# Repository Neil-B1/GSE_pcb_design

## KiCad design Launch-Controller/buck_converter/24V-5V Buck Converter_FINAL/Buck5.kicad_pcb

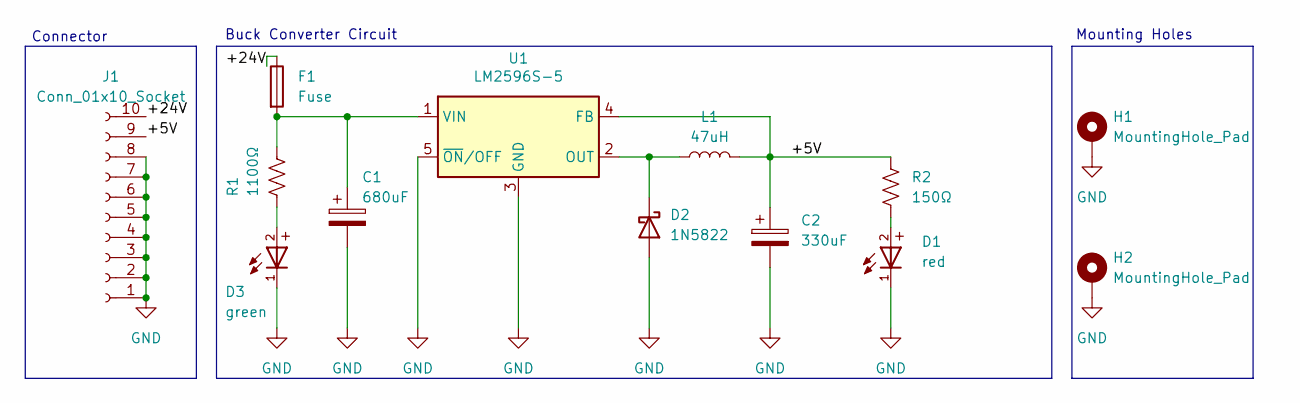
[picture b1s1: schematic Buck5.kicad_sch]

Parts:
C1: 680uF; CAPAE660X800N
C2: 330uF; CP_Radial_D8.0mm_P3.50mm
D1: red; LED_1206_3216Metric_Pad1.42x1.75mm_HandSolder
D2: 1N5822; D_DO-201AD_P15.24mm_Horizontal
D3: green; LED_0603_1608Metric_Pad1.05x0.95mm_HandSolder
F1: Fuse; D_0402_1005Metric_Pad0.77x0.64mm_HandSolder
H1, H2: MountingHole_Pad; MountingHole_3.7mm_Pad
J1: Conn_01x10_Socket; PRECI-DIP_310-87-110-41-001101
L1: 47uH; output inductor
R1: 1100Ω; R_1210_3225Metric_Pad1.30x2.65mm_HandSolder
R2: 150Ω; R_0805_2012Metric_Pad1.20x1.40mm_HandSolder
U1: LM2596S-5; TO-263-5_TabPin3

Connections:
/+5V: C2.1, J1.9, L1.2, R2.1, U1.4 (FB)
/+24V: F1.1, J1.10
GND: C1.2, C2.2, D1.1, D2.2 (A), D3.1, H1.1, H2.1, J1.1, J1.2, J1.3, J1.4, J1.5, J1.6, J1.7, J1.8, U1.3 (GND), U1.5 (~ON/OFF)
unnamed: D1.2, R2.2
unnamed: D2.1 (K), L1.1, U1.2 (OUT)
unnamed: D3.2, R1.2
unnamed: C1.1, F1.2, R1.1, U1.1 (VIN)

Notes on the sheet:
Connector
Buck Converter Circuit
Mounting Holes

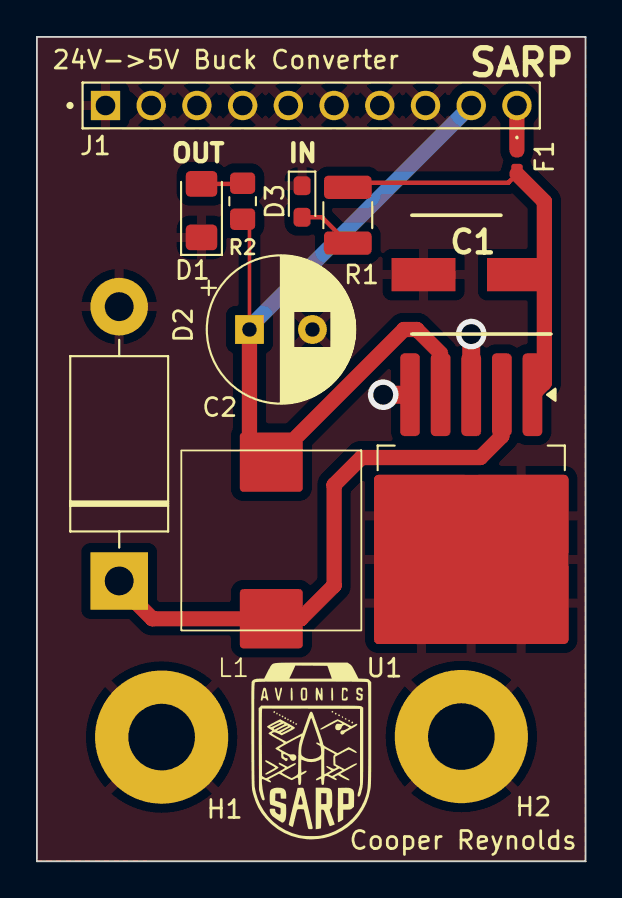
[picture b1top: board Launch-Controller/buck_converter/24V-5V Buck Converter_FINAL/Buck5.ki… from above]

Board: 4 copper layers, 30.5 x 45.8 mm, 13 parts (0 on the bottom side), 7 nets.

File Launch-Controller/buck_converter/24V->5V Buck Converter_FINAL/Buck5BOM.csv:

"Reference","Value","Datasheet","Footprint","Qty","DNP"
"C1","680uF","https://industrial.panasonic.com/cdbs/www-data/pdf/RDE0000/A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","Library:CAPAE660X800N","1",""
"C2","330uF","https://industrial.panasonic.com/cdbs/www-data/pdf/RDF0000/A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","Capacitor_THT:CP_Radial_D8.0mm_P3.50mm","1",""
"D1","red","https://www.mouser.com/datasheet/2/50/SM1206HC-3001920.pdf","LED_SMD:LED_1206_3216Metric_Pad1.42x1.75mm_HandSolder","1",""
"D2","1N5822","http://www.vishay.com/docs/88526/1n5820.pdf","Diode_THT:D_DO-201AD_P15.24mm_Horizontal","1",""
"D3","green","https://www.mouser.com/datasheet/2/50/SM0603PGC-3001706.pdf","LED_SMD:LED_0603_1608Metric_Pad1.05x0.95mm_HandSolder","1",""
"F1","Fuse","https://industrial.panasonic.com/cdbs/www-data/pdf/AFA0000/A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","Diode_SMD:D_0402_1005Metric_Pad0.77x0.64mm_HandSolder","1",""
"J1","Conn_01x10_Socket","https://precidip.com/product/310-87-110-41-001101/","Library:PRECI-DIP_310-87-110-41-001101","1",""
"L1","47uH","bourns.com/docs/Product-Datasheets/SRP1038A.pdf","Library:output inductor","1",""
"R1","1100Ω","https://www.vishay.com/docs/20043/crcwhpe3.pdf","Resistor_SMD:R_1210_3225Metric_Pad1.30x2.65mm_HandSolder","1",""
"R2","150Ω","https://fscdn.rohm.com/en/products/databook/datasheet/passiv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","Resistor_SMD:R_0805_2012Metric_Pad1.20x1.40mm_HandSolder","1",""
"U1","LM2596S-5","http://www.ti.com/lit/ds/symlink/lm2596.pdf","Package_TO_SOT_SMD:TO-263-5_TabPin3","1",""

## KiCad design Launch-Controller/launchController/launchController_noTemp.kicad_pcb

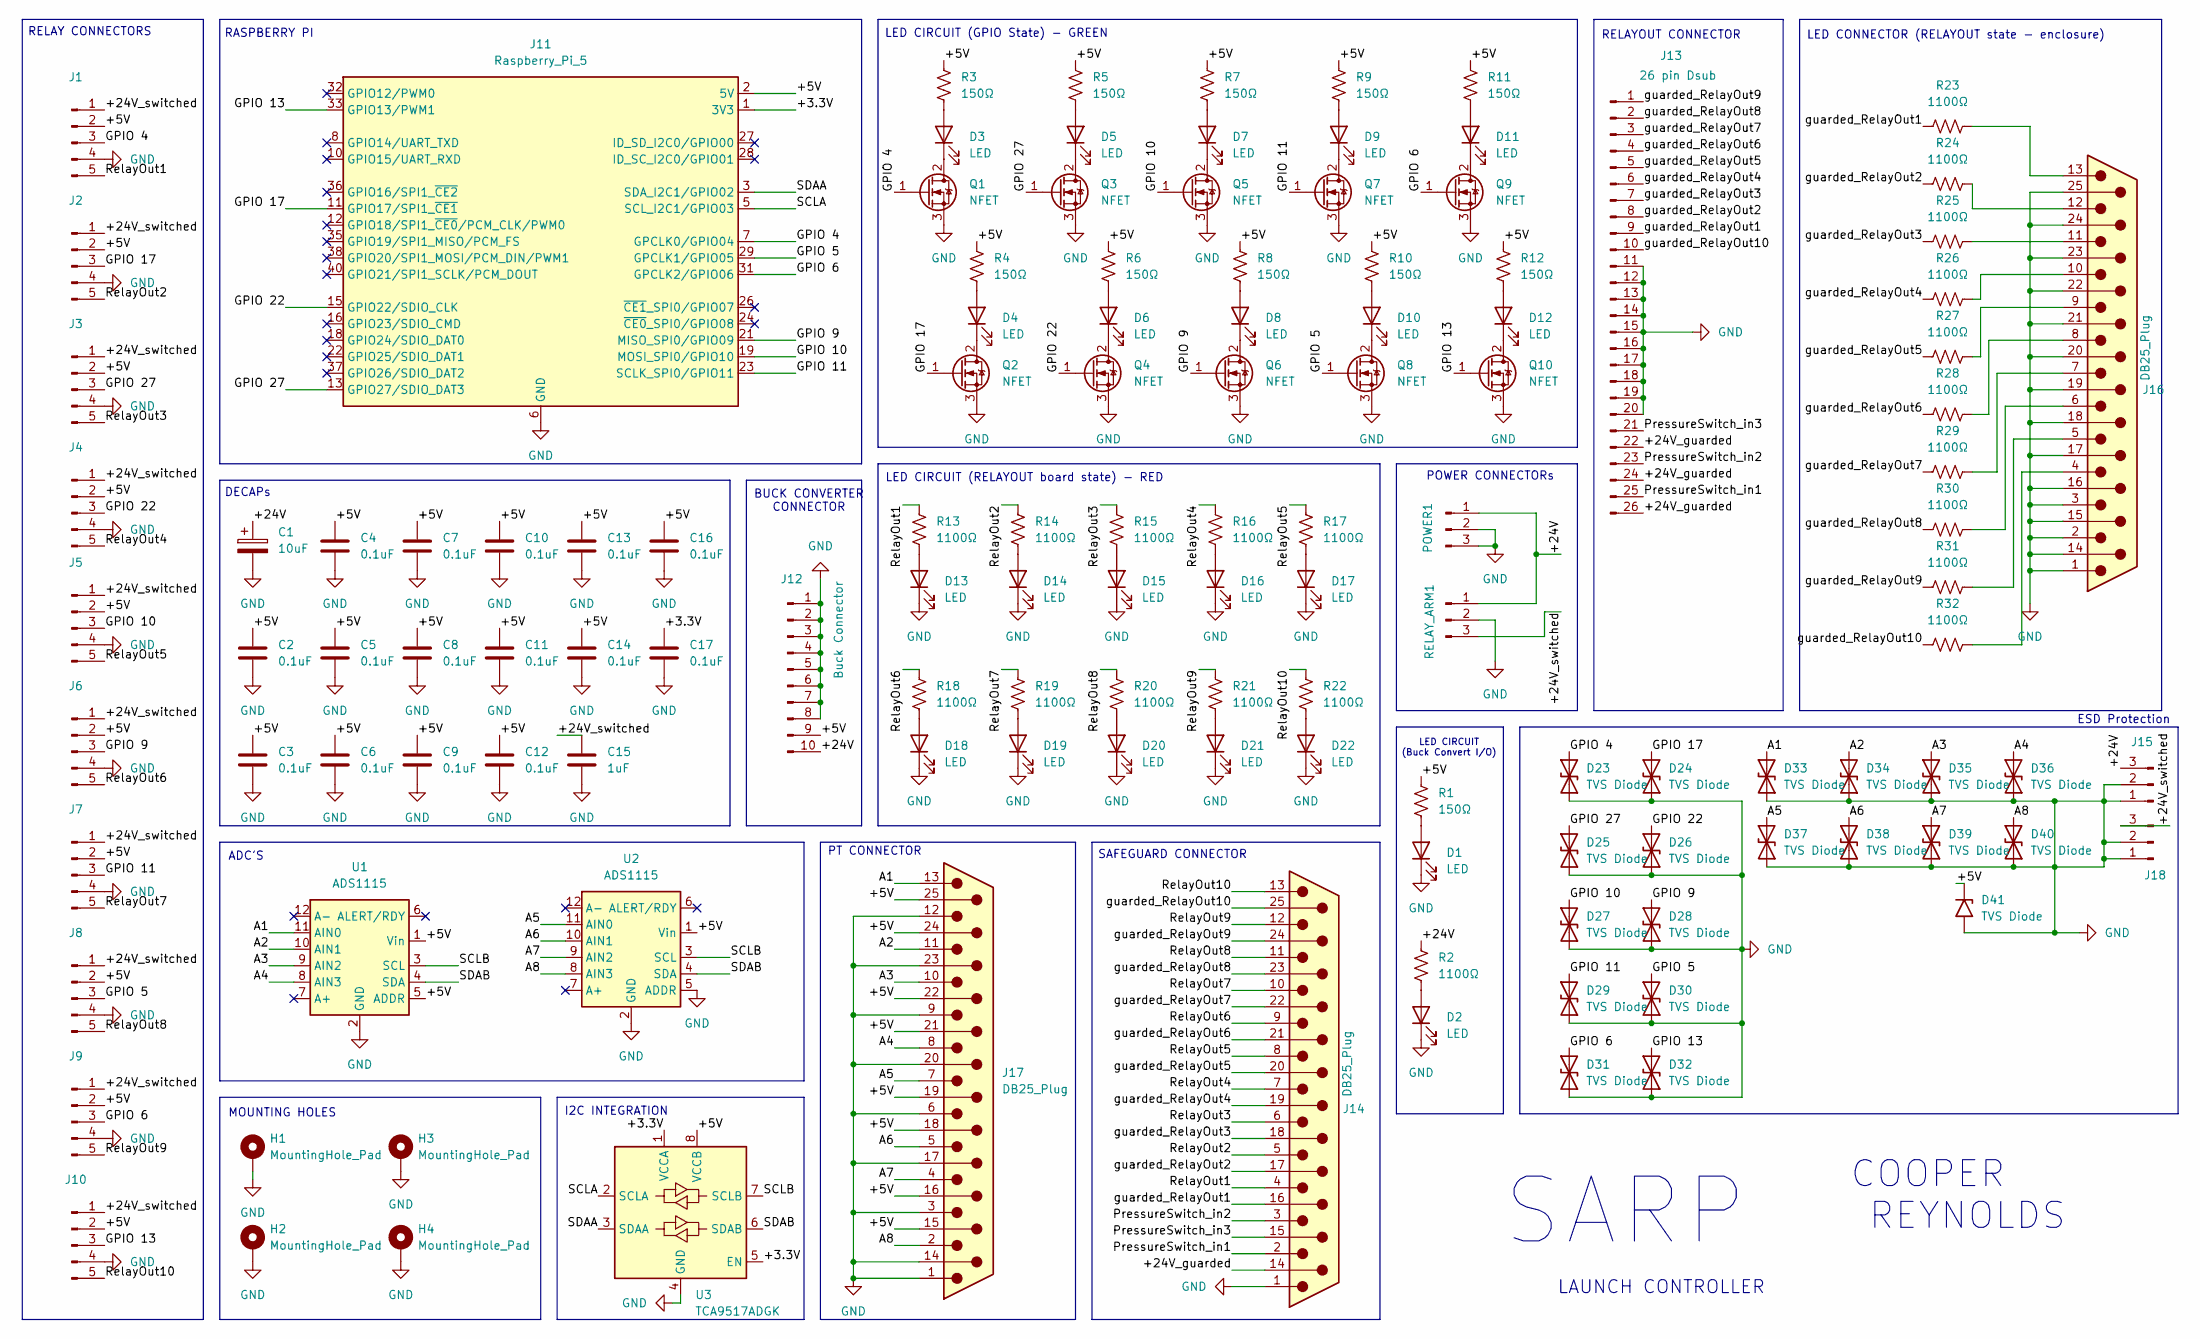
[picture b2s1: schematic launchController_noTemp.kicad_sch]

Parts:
C1: 10uF; CP_Radial_D6.3mm_P2.50mm
C2, C3, C4, C5, C6, C7, C8, C9, C10, C11, C12, C13, C14, C16, C17: 0.1uF; C_0402_1005Metric_Pad0.74x0.62mm_HandSolder
C15: 1uF; C_Axial_L5.1mm_D3.1mm_P7.50mm_Horizontal
D1, D13, D14, D15, D16, D17, D18, D19, D20, D21, D22: LED; LED_1206_3216Metric_Pad1.42x1.75mm_HandSolder
D2, D3, D4, D5, D6, D7, D8, D9, D10, D11, D12: LED; LED_0603_1608Metric_Pad1.05x0.95mm_HandSolder
D23, D24, D25, D26, D27, D28, D29, D30, D31, D32: TVS Diode; D_SOD-923
D33, D34, D35, D36, D37, D38, D39, D40: TVS Diode; D_SOD-523
D41: TVS Diode; D_SOD-323_HandSoldering
H1, H2, H3, H4: MountingHole_Pad; MountingHole_3.7mm_Pad
J1, J2, J3, J4, J5, J6, J7, J8, J9, J10: Relay Connector; RelaySwitch Connector
J11: Raspberry_Pi_5; RPi_5_upside_down
J12: Buck Connector; BuckConverter Connector
J13: 26 pin Dsub; DSUB-26-HD_Female_Horizontal_P2.29x1.98mm_EdgePinOffset8.35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
J14, J16, J17: DB25_Plug; DSUB-25_Female_Horizontal_P2.77x2.84mm_EdgePinOffset7.70mm_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
J15, J18: TVS Diode; SOT-23-3
POWER1: Power Connector; 684M3W3203L461
Q1, Q2, Q3, Q4, Q5, Q6, Q7, Q8, Q9, Q10: NFET; SOT-23-3
R1: 150Ω; R_0805_2012Metric_Pad1.20x1.40mm_HandSolder
R2, R13, R14, R15, R16, R17, R18, R19, R20, R21, R22, R23, R24, R25, R26, R27, R28, R29, R30, R31, R32: 1100Ω; R_1210_3225Metric_Pad1.30x2.65mm_HandSolder
R3, R4, R5, R6, R7, R8, R9, R10, R11, R12: 150Ω; R_0805_2012Metric_Pad1.20x1.40mm_HandSolder
RELAY_ARM1: Power Connector; 684M3W3203L461
U1, U2: ADS1115
U3: TCA9517ADGK; Texas_S-PDSO-G8_3x3mm_P0.65mm

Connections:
/+3.3V: C17.1, J11.1 (3V3), J11.17 (3V3), U3.1 (VCCA), U3.5 (EN)
/+5V: C2.1, C3.1, C4.1, C5.1, C6.1, C7.1, C8.1, C9.1, C10.1, C11.1, C12.1, C13.1, C14.1, C16.1, D41.1 (A1), J1.2, J2.2, J3.2, J4.2, J5.2, J6.2, J7.2, J8.2, J9.2, J10.2, J11.2 (5V), J11.4 (5V), J12.9, J17.15, J17.16, J17.18, J17.19, J17.21, J17.22, J17.24, J17.25, R1.1, R3.1, R4.1, R5.1, R6.1, R7.1, R8.1, R9.1, R10.1, R11.1, R12.1, U1.1 (Vin), U1.5 (ADDR), U2.1 (Vin), U3.8 (VCCB)
/+24V: C1.1, J12.10, J15.3, POWER1.1, R2.1, RELAY_ARM1.1
/+24V_guarded: J13.22, J13.24, J13.26, J14.14
/+24V_switched: C15.1, J1.1, J2.1, J3.1, J4.1, J5.1, J6.1, J7.1, J8.1, J9.1, J10.1, J18.3, RELAY_ARM1.3
/A1: D33.2 (A2), J17.13, U1.11 (AIN0)
/A2: D34.2 (A2), J17.11, U1.10 (AIN1)
/A3: D35.2 (A2), J17.10, U1.9 (AIN2)
/A4: D36.2 (A2), J17.8, U1.8 (AIN3)
/A5: D37.2 (A2), J17.7, U2.11 (AIN0)
/A6: D38.2 (A2), J17.5, U2.10 (AIN1)
/A7: D39.2 (A2), J17.4, U2.9 (AIN2)
/A8: D40.2 (A2), J17.2, U2.8 (AIN3)
/GPIO 4: D23.2 (A2), J1.3, J11.7 (GPCLK0/GPIO04), Q1.1 (G)
/GPIO 5: D30.2 (A2), J8.3, J11.29 (GPCLK1/GPIO05), Q8.1 (G)
/GPIO 6: D31.2 (A2), J9.3, J11.31 (GPCLK2/GPIO06), Q9.1 (G)
/GPIO 9: D28.2 (A2), J6.3, J11.21 (MISO_SPI0/GPIO09), Q6.1 (G)
/GPIO 10: D27.2 (A2), J5.3, J11.19 (MOSI_SPI0/GPIO10), Q5.1 (G)
/GPIO 11: D29.2 (A2), J7.3, J11.23 (SCLK_SPI0/GPIO11), Q7.1 (G)
/GPIO 13: D32.2 (A2), J10.3, J11.33 (GPIO13/PWM1), Q10.1 (G)
/GPIO 17: D24.2 (A2), J2.3, J11.11 (GPIO17/SPI1_~CE1), Q2.1 (G)
/GPIO 22: D26.2 (A2), J4.3, J11.15 (GPIO22/SDIO_CLK), Q4.1 (G)
/GPIO 27: D25.2 (A2), J3.3, J11.13 (GPIO27/SDIO_DAT3), Q3.1 (G)
/PressureSwitch_in1: J13.25, J14.2
/PressureSwitch_in2: J13.23, J14.3
/PressureSwitch_in3: J13.21, J14.15
/RelayOut1: J1.5, J14.4, R13.1
/RelayOut2: J2.5, J14.5, R14.1
/RelayOut3: J3.5, J14.6, R15.1
/RelayOut4: J4.5, J14.7, R16.1
/RelayOut5: J5.5, J14.8, R17.1
/RelayOut6: J6.5, J14.9, R18.1
/RelayOut7: J7.5, J14.10, R19.1
/RelayOut8: J8.5, J14.11, R20.1
/RelayOut9: J9.5, J14.12, R21.1
/RelayOut10: J10.5, J14.13, R22.1
/SCLA: J11.5 (SCL_I2C1/GPIO03), U3.2 (SCLA)
/SCLB: U1.3 (SCL), U2.3 (SCL), U3.7 (SCLB)
/SDAA: J11.3 (SDA_I2C1/GPIO02), U3.3 (SDAA)
/SDAB: U1.4 (SDA), U2.4 (SDA), U3.6 (SDAB)
/guarded_RelayOut1: J13.9, J14.16, R23.1
/guarded_RelayOut2: J13.8, J14.17, R24.1
/guarded_RelayOut3: J13.7, J14.18, R25.1
/guarded_RelayOut4: J13.6, J14.19, R26.1
/guarded_RelayOut5: J13.5, J14.20, R27.1
/guarded_RelayOut6: J13.4, J14.21, R28.1
/guarded_RelayOut7: J13.3, J14.22, R29.1
/guarded_RelayOut8: J13.2, J14.23, R30.1
/guarded_RelayOut9: J13.1, J14.24, R31.1
/guarded_RelayOut10: J13.10, J14.25, R32.1
GND: C1.2, C2.2, C3.2, C4.2, C5.2, C6.2, C7.2, C8.2, C9.2, C10.2, C11.2, C12.2, C13.2, C14.2, C15.2, C16.2, C17.2, D1.1 (K), D2.1 (K), D13.1 (K), D14.1 (K), D15.1 (K), D16.1 (K), D17.1 (K), D18.1 (K), D19.1 (K), D20.1 (K), D21.1 (K), D22.1 (K), D23.1 (A1), D24.1 (A1), D25.1 (A1), D26.1 (A1), D27.1 (A1), D28.1 (A1), D29.1 (A1), D30.1 (A1), D31.1 (A1), D32.1 (A1), D33.1 (A1), D34.1 (A1), D35.1 (A1), D36.1 (A1), D37.1 (A1), D38.1 (A1), D39.1 (A1), D40.1 (A1), D41.2 (A2), H1.1, H2.1, H3.1, H4.1, J1.4, J2.4, J3.4, J4.4, J5.4, J6.4, J7.4, J8.4, J9.4, J10.4, J11.6 (GND), J11.9 (GND), J11.14 (GND), J11.20 (GND), J11.25 (GND), J11.30 (GND), J11.34 (GND), J11.39 (GND), J12.1, J12.2, J12.3, J12.4, J12.5, J12.6, J12.7, J12.8, J13.11, J13.12, J13.13, J13.14, J13.15, J13.16, J13.17, J13.18, J13.19, J13.20, J14.1, J15.1, J15.2, J16.1, J16.2, J16.3, J16.14, J16.15, J16.16, J16.17, J16.18, J16.19, J16.20, J16.21, J16.22, J16.23, J16.24, J16.25, J17.1, J17.3, J17.6, J17.9, J17.12, J17.14, J17.17, J17.20, J17.23, J18.1, J18.2, POWER1.2, POWER1.3, Q1.3 (S), Q2.3 (S), Q3.3 (S), Q4.3 (S), Q5.3 (S), Q6.3 (S), Q7.3 (S), Q8.3 (S), Q9.3 (S), Q10.3 (S), RELAY_ARM1.2, U1.2 (GND), U2.2 (GND), U2.5 (ADDR), U3.4 (GND)
unnamed: D1.2 (A), R1.2
unnamed: D2.2 (A), R2.2
unnamed: D3.2 (A), R3.2
unnamed: D3.1 (K), Q1.2 (D)
unnamed: D4.2 (A), R4.2
unnamed: D4.1 (K), Q2.2 (D)
unnamed: D5.2 (A), R5.2
unnamed: D5.1 (K), Q3.2 (D)
unnamed: D6.2 (A), R6.2
unnamed: D6.1 (K), Q4.2 (D)
unnamed: D7.2 (A), R7.2
unnamed: D7.1 (K), Q5.2 (D)
unnamed: D8.2 (A), R8.2
unnamed: D8.1 (K), Q6.2 (D)
unnamed: D9.2 (A), R9.2
unnamed: D9.1 (K), Q7.2 (D)
unnamed: D10.2 (A), R10.2
unnamed: D10.1 (K), Q8.2 (D)
unnamed: D11.2 (A), R11.2
unnamed: D11.1 (K), Q9.2 (D)
unnamed: D12.2 (A), R12.2
unnamed: D12.1 (K), Q10.2 (D)
unnamed: D13.2 (A), R13.2
unnamed: D14.2 (A), R14.2
unnamed: D15.2 (A), R15.2
unnamed: D16.2 (A), R16.2
unnamed: D17.2 (A), R17.2
unnamed: D18.2 (A), R18.2
unnamed: D19.2 (A), R19.2
unnamed: D20.2 (A), R20.2
unnamed: D21.2 (A), R21.2
unnamed: D22.2 (A), R22.2
unnamed: J16.4, R32.2
unnamed: J16.5, R31.2
unnamed: J16.6, R30.2
unnamed: J16.7, R29.2
unnamed: J16.8, R28.2
unnamed: J16.9, R27.2
unnamed: J16.10, R26.2
unnamed: J16.11, R25.2
unnamed: J16.12, R24.2
unnamed: J16.13, R23.2

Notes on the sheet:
SAFEGUARD CONNECTOR
LED CONNECTOR (RELAYOUT state - enclosure)
I2C INTEGRATION
LAUNCH CONTROLLER
LED CIRCUIT (Buck Convert I/O)
MOUNTING HOLES
ESD Protection
RELAY CONNECTORS
LED CIRCUIT (GPIO State) - GREEN
POWER CONNECTORs
BUCK CONVERTER CONNECTOR
SARP
COOPER REYNOLDS
DECAPs
RELAYOUT CONNECTOR
RASPBERRY PI
LED CIRCUIT (RELAYOUT board state) - RED
ADC'S
PT CONNECTOR

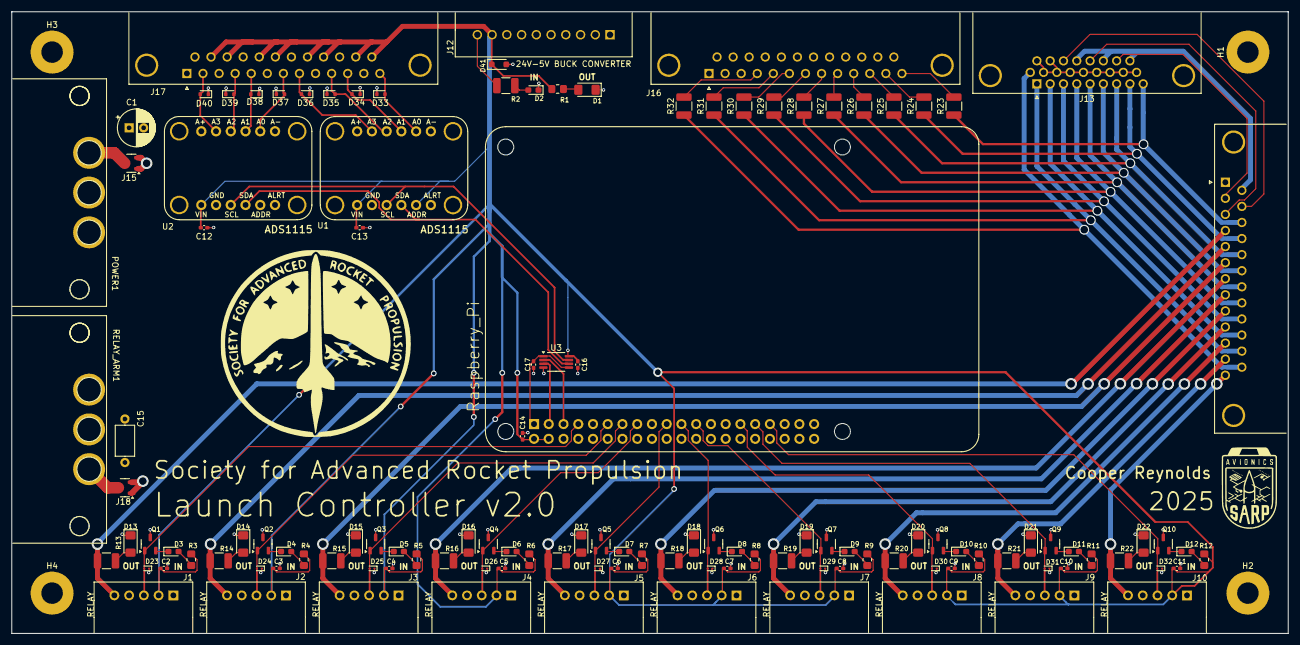
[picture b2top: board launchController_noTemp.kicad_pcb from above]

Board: 4 copper layers, 219.9 x 107.1 mm, 128 parts (0 on the bottom side), 93 nets.

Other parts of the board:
G1: LOGO; round sarp

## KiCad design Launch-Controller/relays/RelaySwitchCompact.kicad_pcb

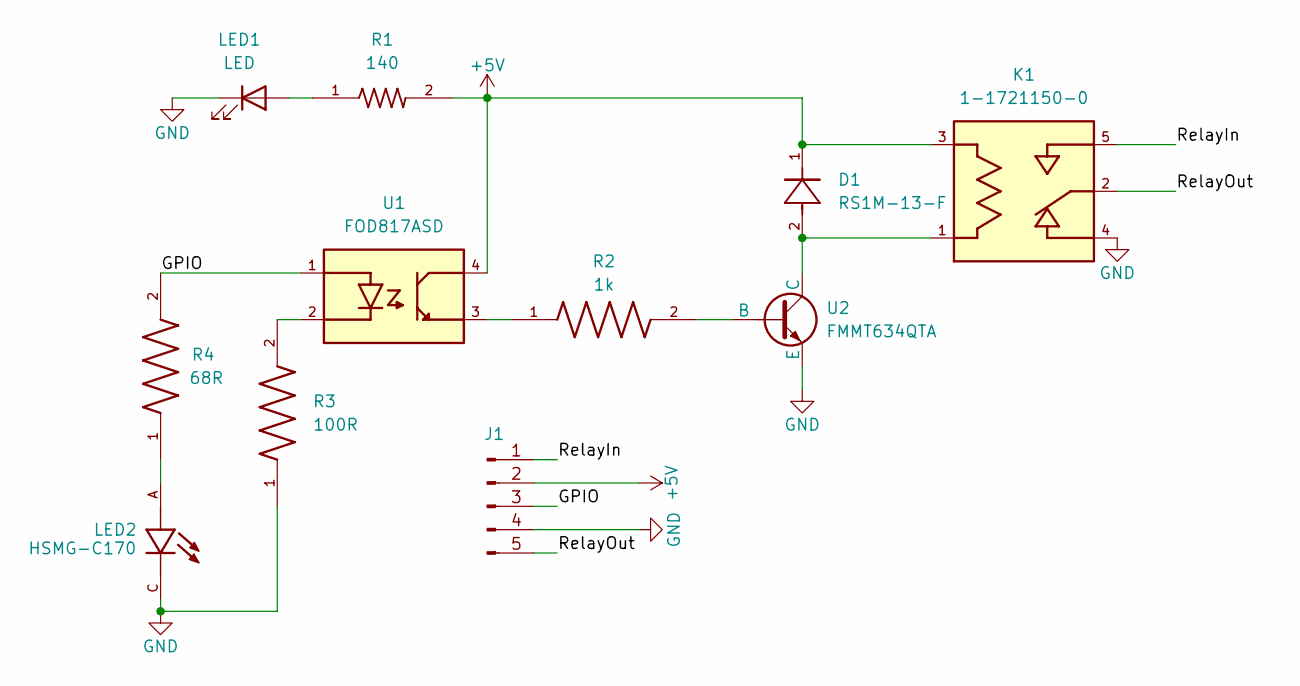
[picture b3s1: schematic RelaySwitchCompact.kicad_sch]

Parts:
D1: RS1M-13-F; SMA_DIO-M; MANUFACTURER_PART_NUMBER RS1M-13-F
J1: 350-10-105-00-001101; PinHeader_1x05_P2.54mm_Vertical
K1: 1-1721150-0; RELAY_1-1721150-0; PARTREV D
LED1: LED; LED_SML-D12V1WT86
LED2: HSMG-C170; LED_HSMS-C170; PARTREV March 25, 2022
R1: 140; RESC1607X60N
R2: 1k; RESC1608X50N
R3: 100R; RESC1608X55N
R4: 68R; RESC1005X35N
U1: FOD817ASD; SOIC254P1016X385-4N
U2: FMMT634QTA; VREG_XC6206P282MR-G

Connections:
+5V: D1.1, J1.2, K1.3, R1.2, U1.4
/GPIO: J1.3, R4.2, U1.1
/RelayIn: J1.1, K1.5
/RelayOut: J1.5, K1.2
GND: J1.4, K1.4, LED1.1 (K), LED2.C, R3.1, U2.3 (E); also elsewhere on the board
unnamed: LED1.2 (A), R1.1
unnamed: LED2.A, R4.1
unnamed: R2.1, U1.3
unnamed: R3.2, U1.2
unnamed: R2.2, U2.2 (B)
unnamed: D1.2, K1.1, U2.1 (C)

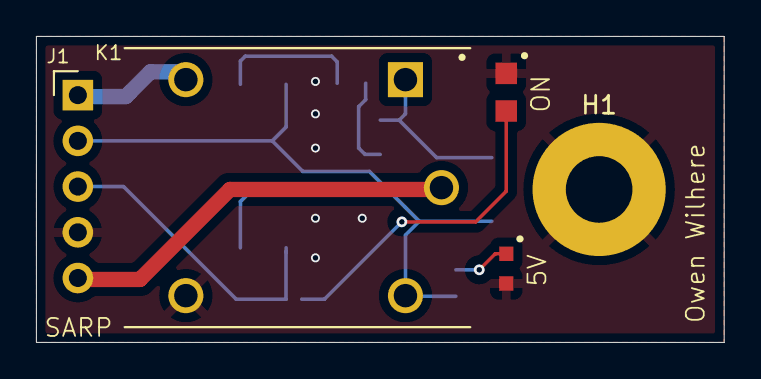
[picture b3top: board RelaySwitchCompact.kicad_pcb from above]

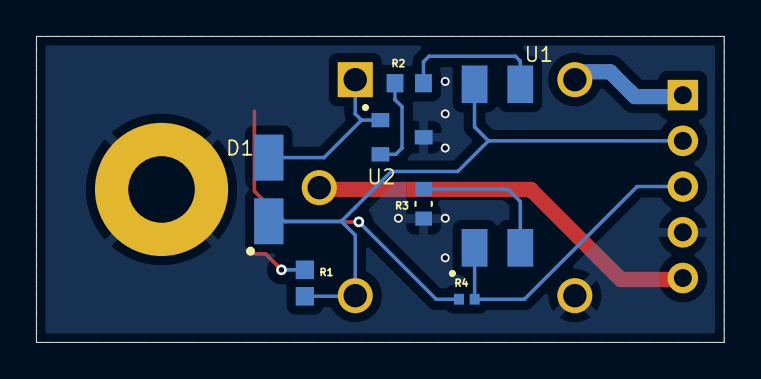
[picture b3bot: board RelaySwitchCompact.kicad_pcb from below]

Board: 2 copper layers, 38.2 x 17.0 mm, 12 parts (7 on the bottom side), 11 nets.

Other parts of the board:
H1: MountingHole_Pad; MountingHole_3.7mm_Pad

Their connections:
GND: H1.1; also elsewhere on the board

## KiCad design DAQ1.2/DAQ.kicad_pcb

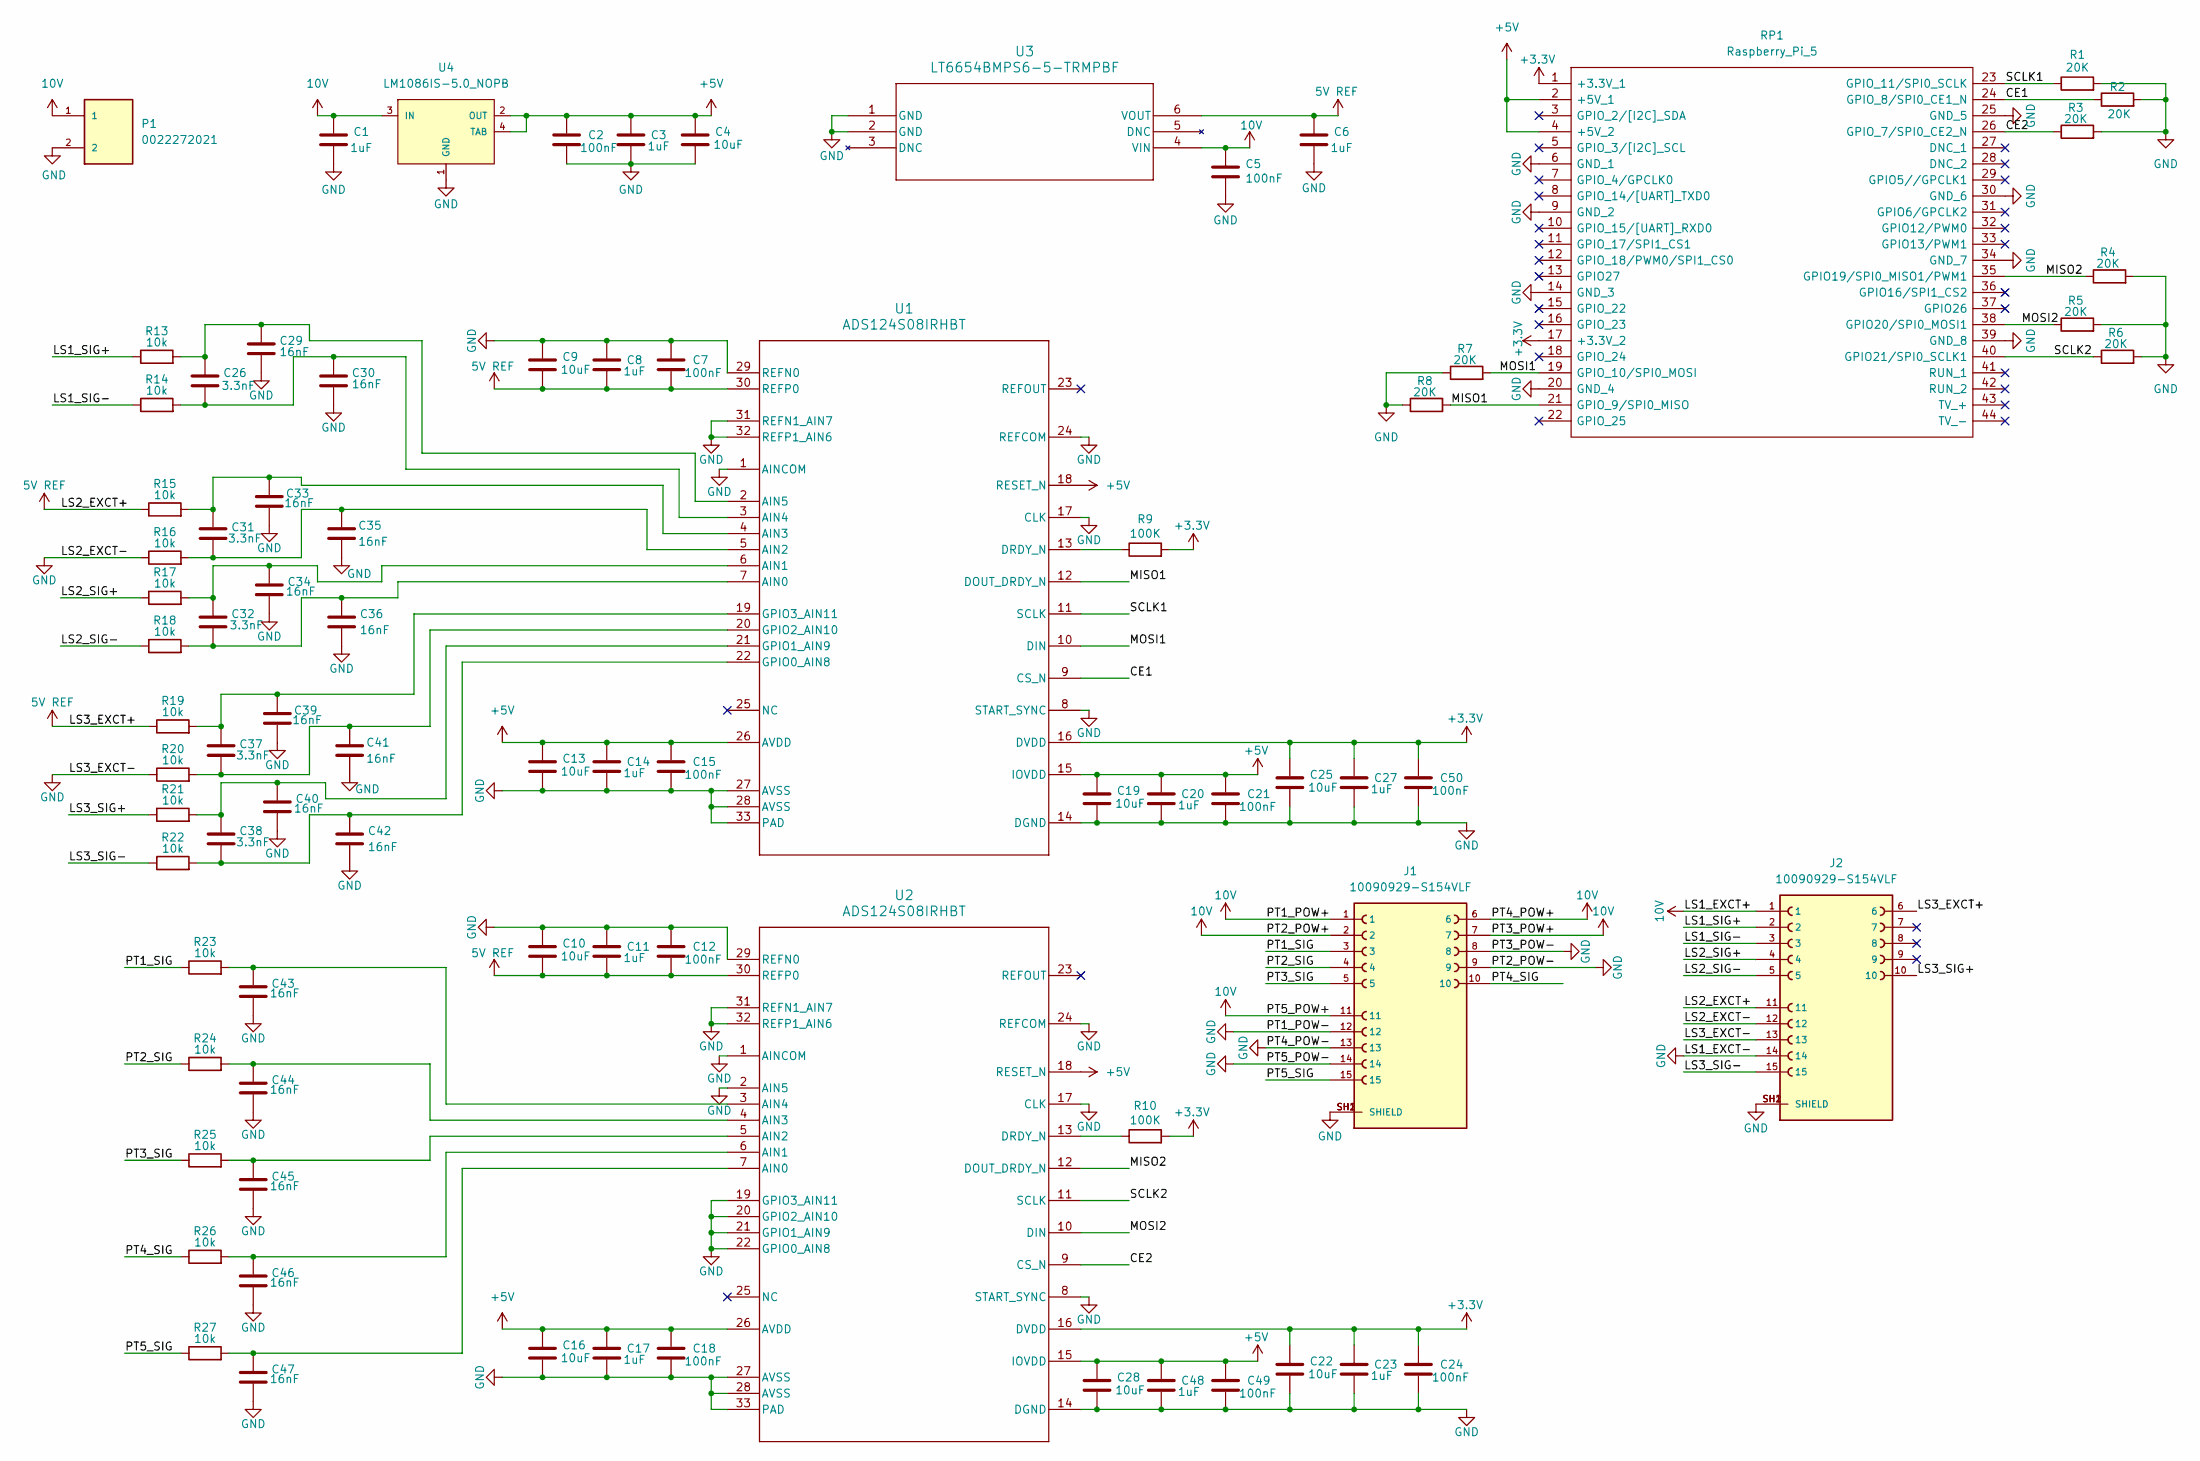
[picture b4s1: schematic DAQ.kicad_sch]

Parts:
C1, C3, C6, C8, C11, C14, C17, C20, C23, C27, C48: 1uF; CAPC1608X94N
C2, C5, C7, C12, C15, C18, C21, C24, C49, C50: 100nF; CAPC1608X97N
C4, C9, C10, C13, C16, C19, C22, C25, C28: 10uF; CAPC2012X145N
C26, C31, C32, C37, C38: 3.3nF; CAP_CL10_SAM
C29, C30, C33, C34, C35, C36, C39, C40, C41, C42, C43, C44, C45, C46, C47: 16nF; CAPC3216X95N
J1, J2: 10090929-S154VLF; AMPHENOL_10090929-S154VLF; PARTREV H
P1: 0022272021; MOLEX_0022272021
R1, R2, R3, R4, R5, R6, R7, R8: 20K; RESC1508X50N
R9, R10: 100K; RESC1508X50N
R13, R14, R15, R16, R17, R18, R19, R20, R21, R22, R23, R24, R25, R26, R27: 10k; RC0603N_YAG-M
RP1: Raspberry_Pi_5; raspberrypi_2_3; Manufacturer_Part_Number Raspberry Pi 2 or 3
U1, U2: ADS124S08IRHBT; RHB0032M
U3: LT6654BMPS6-5-TRMPBF; TSOT-23_S6_LIT
U4: LM1086IS-5.0_NOPB; TO254P1524X483-4N

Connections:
5V REF: C6.1, C7.2, C8.2, C9.2, C10.2, C11.2, C12.2, J2.6, J2.11, R15.1, R19.1, U1.30 (REFP0), U2.30 (REFP0), U3.6 (VOUT)
10V: C1.1, C5.1, J1.1, J1.2, J1.6, J1.7, J1.11, J2.1, P1.1, U3.4 (VIN), U4.3 (IN)
/CE1: R2.1, RP1.24 (GPIO_8/SPI0_CE1_N), U1.9 (CS_N)
/CE2: R3.1, RP1.26 (GPIO_7/SPI0_CE2_N), U2.9 (CS_N)
/LS1_SIG+: J2.2, R13.1
/LS1_SIG-: J2.3, R14.1
/LS2_SIG+: J2.4, R17.1
/LS2_SIG-: J2.5, R18.1
/LS3_SIG+: J2.10, R21.1
/LS3_SIG-: J2.15, R22.1
/MISO1: R8.2, RP1.21 (GPIO_9/SPI0_MISO), U1.12 (DOUT_DRDY_N)
/MISO2: R4.1, RP1.35 (GPIO19/SPI0_MISO1/PWM1), U2.12 (DOUT_DRDY_N)
/MOSI1: R7.2, RP1.19 (GPIO_10/SPI0_MOSI), U1.10 (DIN)
/MOSI2: R5.1, RP1.38 (GPIO20/SPI0_MOSI1), U2.10 (DIN)
/PT1_SIG: J1.3, R23.1
/PT2_SIG: J1.4, R24.1
/PT3_SIG: J1.5, R25.1
/PT4_SIG: J1.10, R26.1
/PT5_SIG: J1.15, R27.1
/SCLK1: R1.1, RP1.23 (GPIO_11/SPI0_SCLK), U1.11 (SCLK)
/SCLK2: R6.1, RP1.40 (GPIO21/SPI0_SCLK1), U2.11 (SCLK)
GND: C1.2, C2.2, C3.2, C4.2, C5.2, C6.2, C7.1, C8.1, C9.1, C10.1, C11.1, C12.1, C13.2, C14.2, C15.2, C16.2, C17.2, C18.2, C19.2, C20.2, C21.2, C22.2, C23.2, C24.2, C25.2, C27.2, C28.2, C29.2, C30.2, C33.2, C34.2, C35.2, C36.2, C39.2, C40.2, C41.2, C42.2, C43.2, C44.2, C45.2, C46.2, C47.2, C48.2, C49.2, C50.2, J1.8, J1.9, J1.12, J1.13, J1.14, J1.SH1 (SHIELD), J1.SH2 (SHIELD), J2.12, J2.13, J2.14, J2.SH1 (SHIELD), J2.SH2 (SHIELD), P1.2, R1.2, R2.2, R3.2, R4.2, R5.2, R6.2, R7.1, R8.1, R16.1, R20.1, RP1.6 (GND_1), RP1.9 (GND_2), RP1.14 (GND_3), RP1.20 (GND_4), RP1.25 (GND_5), RP1.30 (GND_6), RP1.34 (GND_7), RP1.39 (GND_8), U1.1 (AINCOM), U1.8 (START_SYNC), U1.14 (DGND), U1.17 (CLK), U1.24 (REFCOM), U1.27 (AVSS), U1.28 (AVSS), U1.29 (REFN0), U1.31 (REFN1_AIN7), U1.32 (REFP1_AIN6), U1.33 (PAD), U2.1 (AINCOM), U2.2 (AIN5), U2.8 (START_SYNC), U2.14 (DGND), U2.17 (CLK), U2.19 (GPIO3_AIN11), U2.20 (GPIO2_AIN10), U2.21 (GPIO1_AIN9), U2.22 (GPIO0_AIN8), U2.24 (REFCOM), U2.27 (AVSS), U2.28 (AVSS), U2.29 (REFN0), U2.31 (REFN1_AIN7), U2.32 (REFP1_AIN6), U2.33 (PAD), U3.1 (GND), U3.2 (GND), U4.1 (GND)
unnamed: C32.2, C36.1, R18.2, U1.7 (AIN0)
unnamed: C32.1, C34.1, R17.2, U1.6 (AIN1)
unnamed: C31.2, C35.1, R16.2, U1.5 (AIN2)
unnamed: C31.1, C33.1, R15.2, U1.4 (AIN3)
unnamed: C26.2, C30.1, R14.2, U1.3 (AIN4)
unnamed: C26.1, C29.1, R13.2, U1.2 (AIN5)
unnamed: R9.1, U1.13 (DRDY_N)
unnamed: C38.2, C42.1, R22.2, U1.22 (GPIO0_AIN8)
unnamed: C38.1, C40.1, R21.2, U1.21 (GPIO1_AIN9)
unnamed: C37.2, C41.1, R20.2, U1.20 (GPIO2_AIN10)
unnamed: C37.1, C39.1, R19.2, U1.19 (GPIO3_AIN11)
unnamed: C47.1, R27.2, U2.7 (AIN0)
unnamed: C46.1, R26.2, U2.6 (AIN1)
unnamed: C45.1, R25.2, U2.5 (AIN2)
unnamed: C44.1, R24.2, U2.4 (AIN3)
unnamed: C43.1, R23.2, U2.3 (AIN4)
unnamed: R10.1, U2.13 (DRDY_N)

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
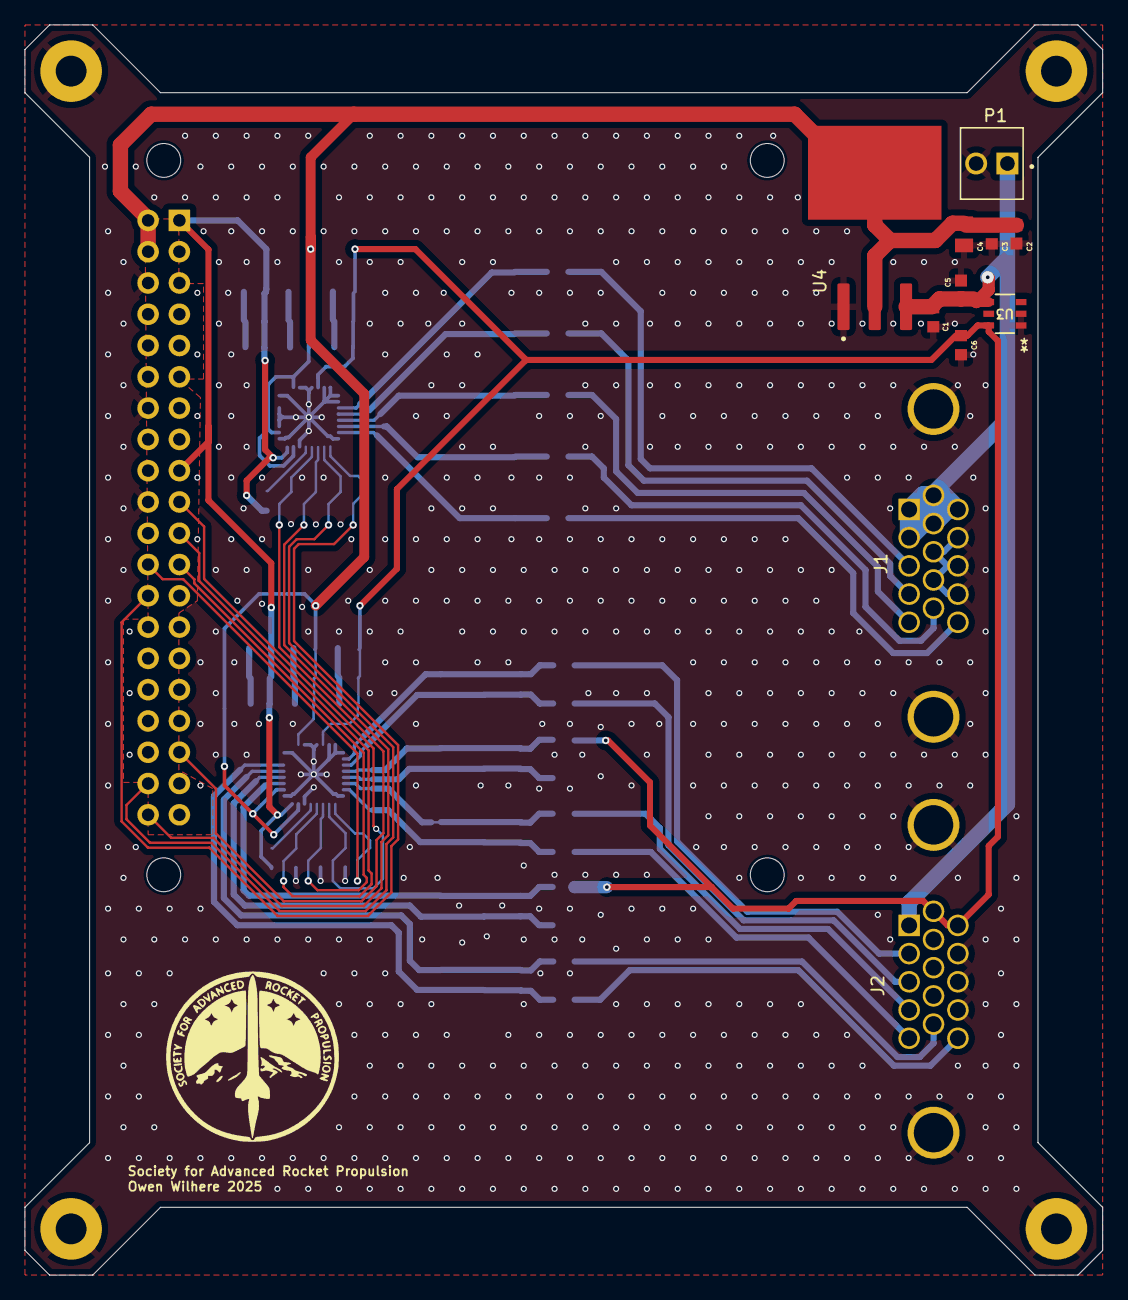
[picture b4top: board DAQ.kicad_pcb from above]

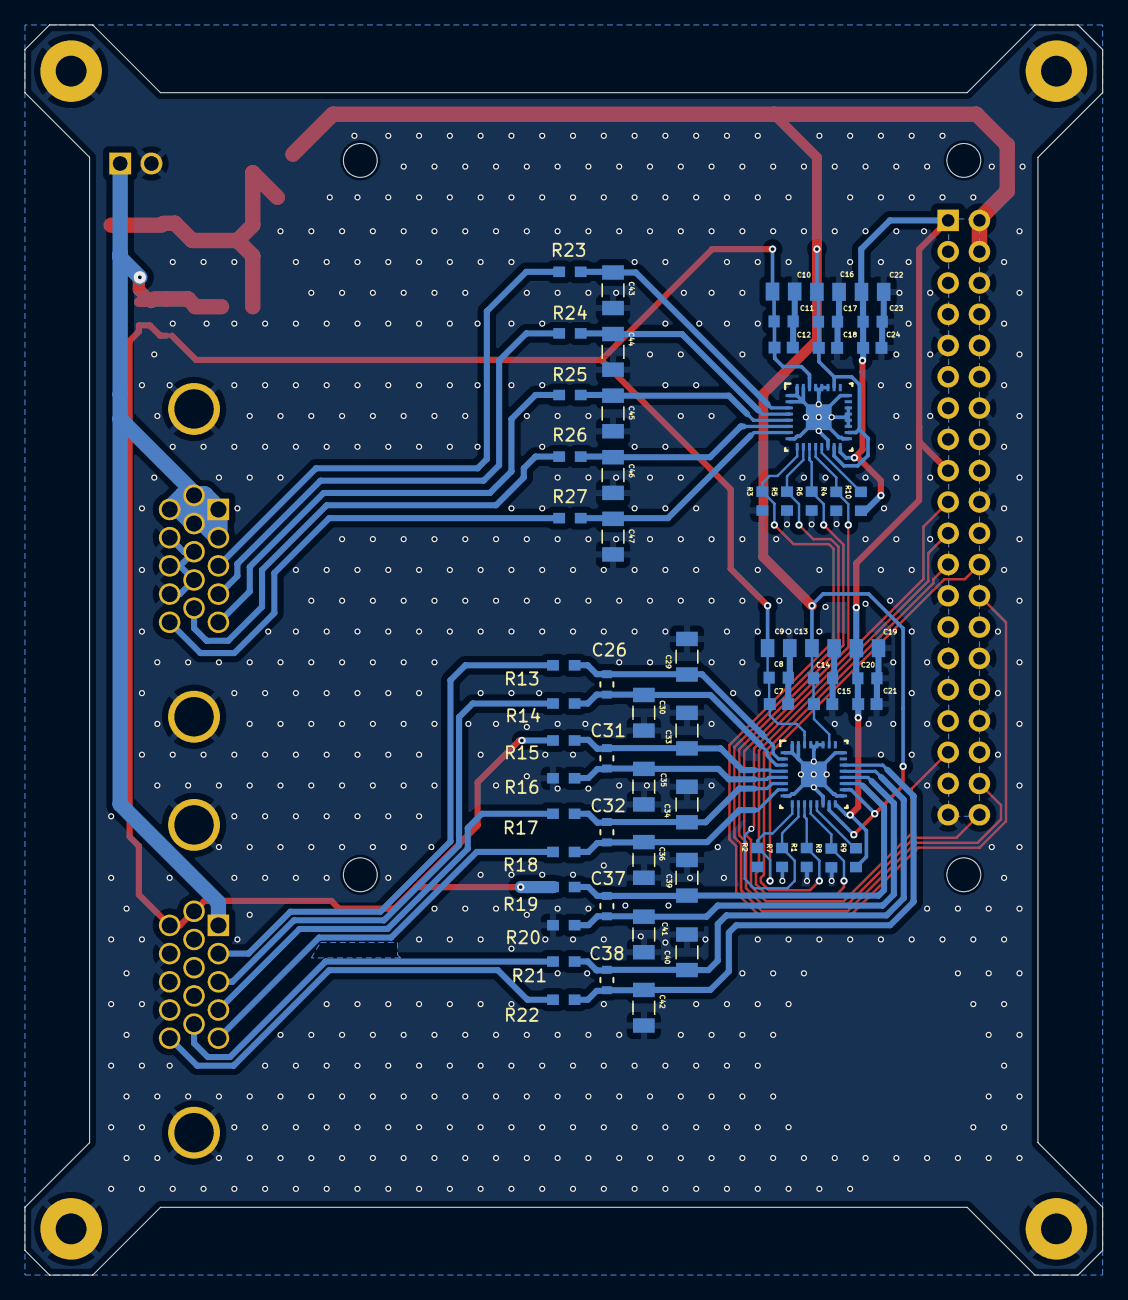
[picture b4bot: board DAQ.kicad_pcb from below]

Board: 2 copper layers, 87.5 x 101.5 mm, 77 parts (66 on the bottom side), 41 nets.

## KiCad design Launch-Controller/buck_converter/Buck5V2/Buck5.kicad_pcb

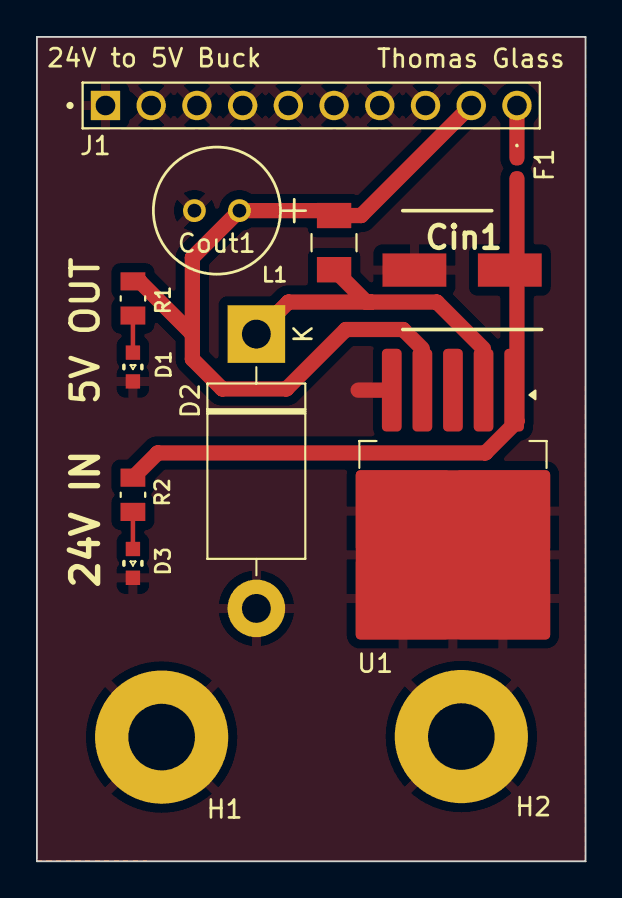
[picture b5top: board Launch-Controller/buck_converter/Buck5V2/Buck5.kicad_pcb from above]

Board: 4 copper layers, 30.5 x 45.8 mm, 13 parts (0 on the bottom side), 7 nets.

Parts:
Cin1: 680u; CAPAE660X800N
Cout1: 220u; CAP_YX_6P3X11_RUB
D1: 150060VS75000; WL-SMCW_0603
D2: 1N5822; D_DO-201AD_P15.24mm_Horizontal
D3: 150060RS75000; WL-SMCW_0603
F1: Fuse; D_0402_1005Metric_Pad0.77x0.64mm_HandSolder
H1, H2: MountingHole_Pad; MountingHole_3.7mm_Pad
J1: Conn_01x10_Socket; PRECI-DIP_310-87-110-41-001101
L1: 33u; INDM3225X240N
R1, R2: 1.1k; RESC2012X65N
U1: LM2596S-5; TO-263-5_TabPin3

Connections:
/+5V: Cout1.1, J1.9, L1.2, R1.1, U1.4 (FB)
/+24V: F1.1, J1.10
GND: Cin1.2, Cout1.2, D1.1, D2.2 (A), D3.1, H1.1, H2.1, J1.1, J1.2, J1.3, J1.4, J1.5, J1.6, J1.7, J1.8, U1.3 (GND), U1.5 (~ON/OFF)
unnamed: D1.2, R1.2
unnamed: D2.1 (K), L1.1, U1.2 (OUT)
unnamed: D3.2, R2.2
unnamed: Cin1.1, F1.2, R2.1, U1.1 (VIN)

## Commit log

2025-02-18 new design repo
2025-02-24 dimensions
2025-02-25 pushed edits
2025-02-28 fixed edge cut
2025-03-11 lc final draft
2025-03-12 pretty board
2025-03-12 buck converter mounting hole and dimension changes
2025-03-12 LC cosmetic updates
2025-03-12 mounting hole changes on relay
2025-03-12 polished launch controller layout
2025-03-14 logic shifter in LC, cleaning up buck_5v
2025-03-14 buck converter v2 changes
2025-03-14 fized relay
2025-03-14 more relay changes
2025-03-15 redone buck converter
2025-03-15 relay final
2025-03-15 finalized relay board
2025-03-16 gerbers generated for buck and main board
2025-03-16 gerbers for buck and main board
2025-03-16 added BOM for buck and main
2025-03-17 fab_files finalized
2025-03-17 final
2025-03-18 renamed buck file
2025-03-18 via ground stitching main board
2025-03-18 via threading buck converter
2025-05-16 added assembly pdf files for edgecuts, f_fab, f_silkscreen, b_fab, b_silksreen, and pick and place files for top and bottom (all for relays)
2025-10-02 add html bom
2025-10-04 Created 10A buck converter schematic
    Uses LMZ13610TZ

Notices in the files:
parts and their libraries:
COPYRIGHT: Copyright (C) 2023 Ultra Librarian. All rights reserved.
